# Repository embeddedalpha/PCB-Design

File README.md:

# PCB-Design    
Repository for PCB Design Projects

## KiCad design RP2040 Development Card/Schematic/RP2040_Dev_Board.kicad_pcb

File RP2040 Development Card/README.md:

# Raspberry Pi RP2040 Development Card

### Schematic : [RP2040_Dev_Board.pdf](https://github.com/embeddedalpha/PCB-Design/files/5889168/RP2040_Dev_Board.pdf)

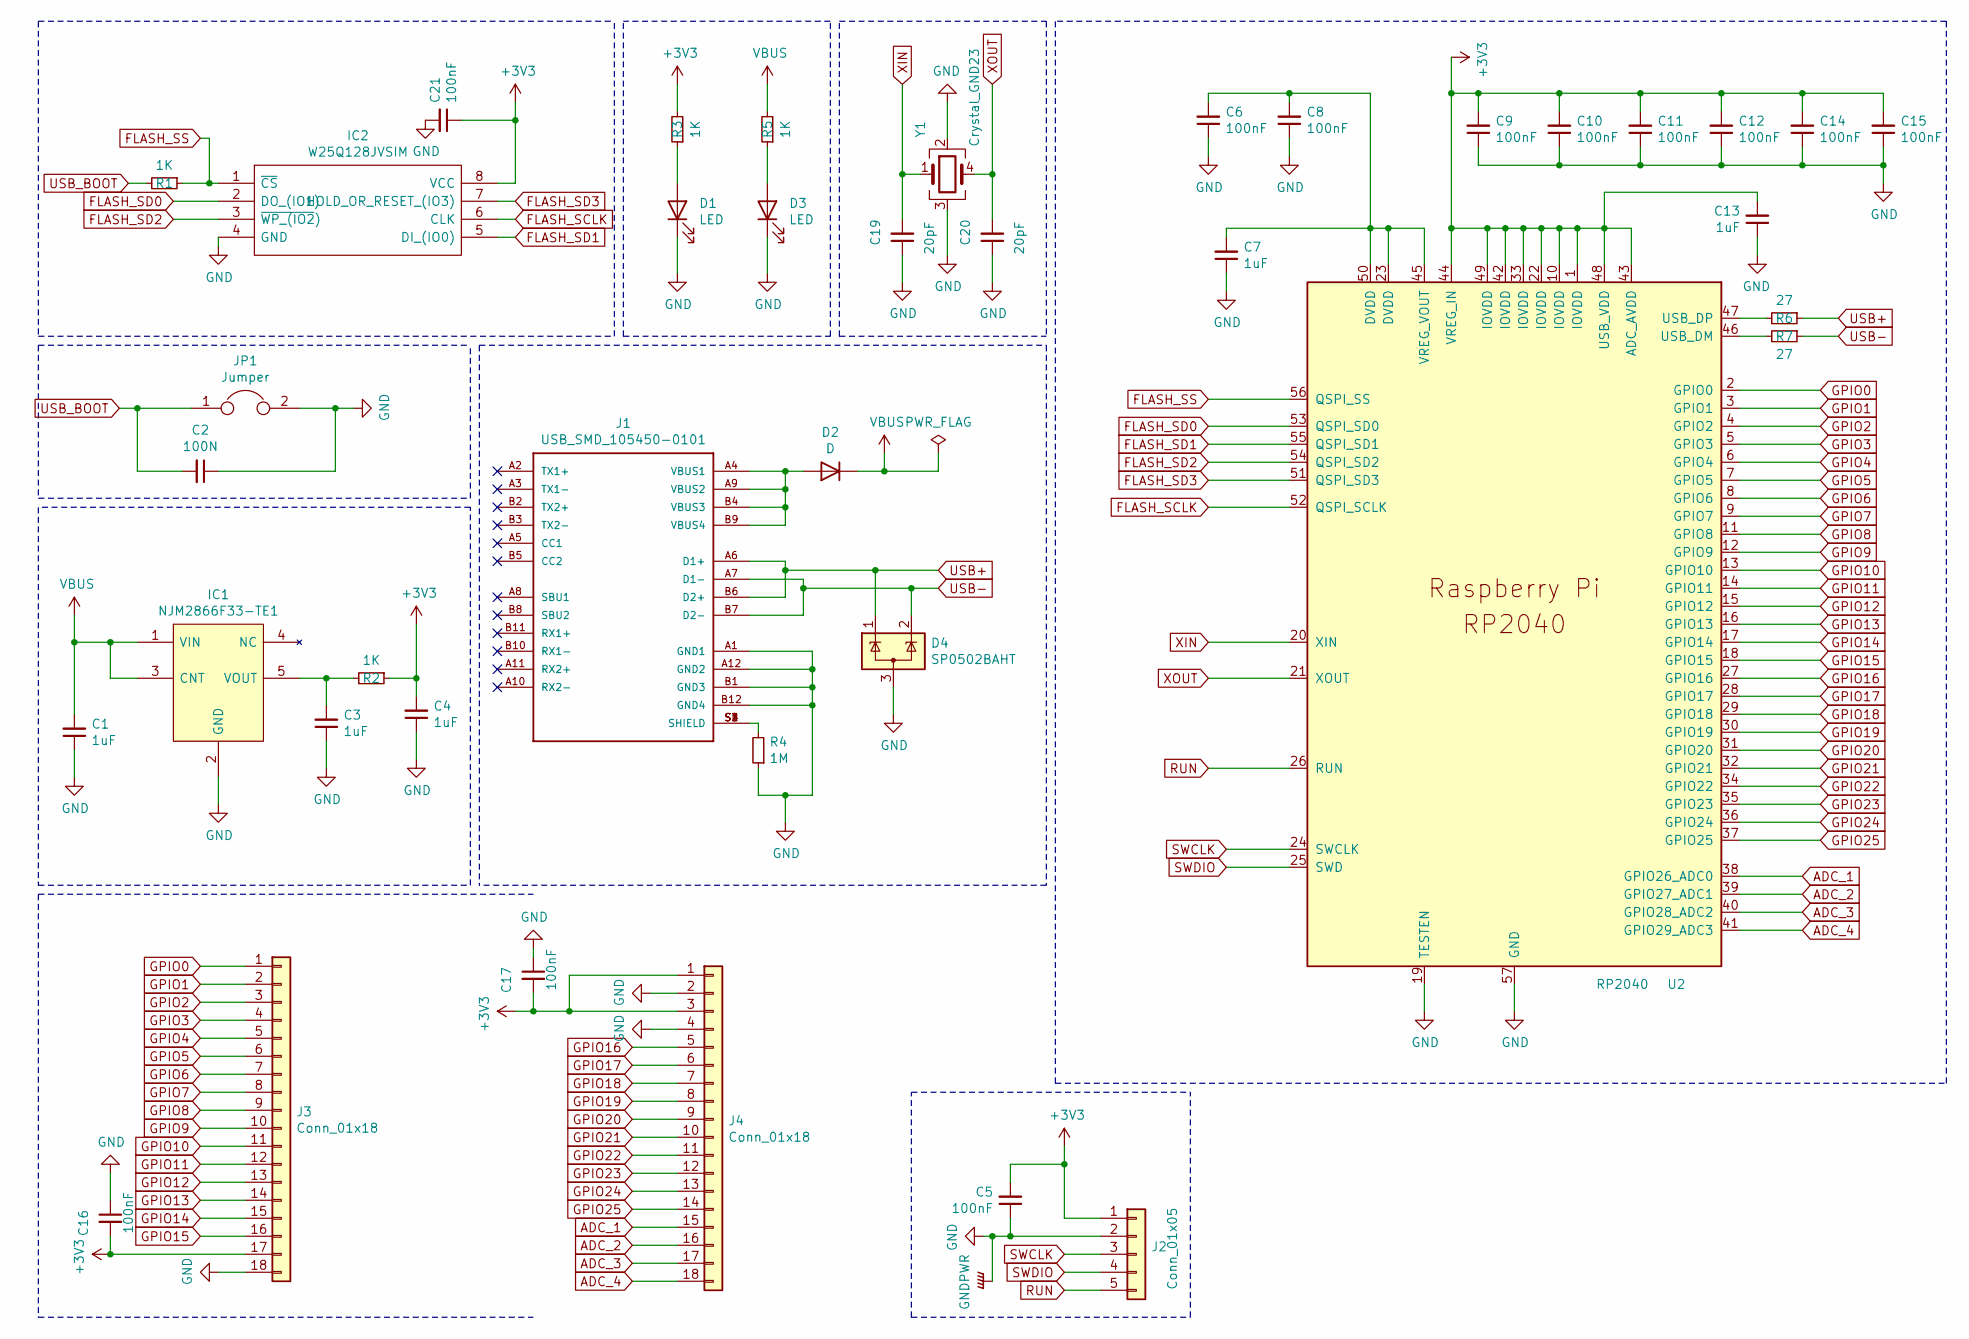
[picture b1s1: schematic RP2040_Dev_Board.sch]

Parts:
C1, C3, C4, C7, C13: 1uF; C_0402_1005Metric
C2: 100N; C_0402_1005Metric
C5, C6, C8, C9, C10, C11, C12, C14, C15, C16, C17, C21: 100nF; C_0402_1005Metric
C19, C20: 20pF; C_0402_1005Metric
D1, D3: LED; LED_0402_1005Metric
D2: D; D_0402_1005Metric
D4: SP0502BAHT; SOT-23
IC1: NJM2866F33-TE1; SOT95P280X130-5N; Mouser Part Number 513-NJM2866F33-TE1
IC2: W25Q128JVSIM; SOIC127P790X216-8N; Mouser Part Number 454-W25Q128JVSIM
J1: USB_SMD_105450-0101; MOLEX_105450-0101
J2: Conn_01x05; PinHeader_1x05_P2.54mm_Vertical
J3: Conn_01x18; Gold_Finger_1x18
J4: Conn_01x18; Gold_Finger_1x18B
JP1: Jumper
R1, R2, R3, R5: 1K; R_0402_1005Metric
R4: 1M; R_0402_1005Metric
R6, R7: 27; R_0402_1005Metric
U2: RP2040; RP2040-QFN-56
Y1: Crystal_GND23; ABM8AIG8000MHZ1ZT

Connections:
+3V3: C4.2, C5.2, C9.2, C10.2, C11.2, C12.2, C13.2, C14.2, C15.2, C16.2, C17.2, C21.1, IC2.8 (VCC), J2.1, J3.17, J4.1, J4.3, R2.1, R3.2, U2.1 (IOVDD), U2.10 (IOVDD), U2.22 (IOVDD), U2.33 (IOVDD), U2.42 (IOVDD), U2.43 (ADC_AVDD), U2.44 (VREG_IN), U2.48 (USB_VDD), U2.49 (IOVDD)
ADC_1: J4.15, U2.38 (GPIO26_ADC0)
ADC_2: J4.16, U2.39 (GPIO27_ADC1)
ADC_3: J4.17, U2.40 (GPIO28_ADC2)
ADC_4: J4.18, U2.41 (GPIO29_ADC3)
FLASH_SCLK: IC2.6 (CLK), U2.52 (QSPI_SCLK)
FLASH_SD0: IC2.2 (DO_(IO1)), U2.53 (QSPI_SD0)
FLASH_SD1: IC2.5 (DI_(IO0)), U2.55 (QSPI_SD1)
FLASH_SD2: IC2.3 (~WP_(IO2)), U2.54 (QSPI_SD2)
FLASH_SD3: IC2.7 (HOLD_OR_RESET_(IO3)), U2.51 (QSPI_SD3)
FLASH_SS: IC2.1 (~CS), R1.1, U2.56 (QSPI_SS)
GND: C1.1, C2.1, C3.1, C4.1, C5.1, C6.1, C7.1, C8.1, C9.1, C10.1, C11.1, C12.1, C13.1, C14.1, C15.1, C16.1, C17.1, C19.1, C20.1, C21.2, D1.1 (K), D3.1 (K), D4.3 (A), IC1.2 (GND), IC2.4 (GND), J1.A1 (GND1), J1.A12 (GND2), J1.B1 (GND3), J1.B12 (GND4), J2.2, J3.18, J4.2, J4.4, JP1.2, R4.1, U2.19 (TESTEN), U2.57 (GND), Y1.2, Y1.3
GPIO0: J3.1, U2.2 (GPIO0)
GPIO1: J3.2, U2.3 (GPIO1)
GPIO2: J3.3, U2.4 (GPIO2)
GPIO3: J3.4, U2.5 (GPIO3)
GPIO4: J3.5, U2.6 (GPIO4)
GPIO5: J3.6, U2.7 (GPIO5)
GPIO6: J3.7, U2.8 (GPIO6)
GPIO7: J3.8, U2.9 (GPIO7)
GPIO8: J3.9, U2.11 (GPIO8)
GPIO9: J3.10, U2.12 (GPIO9)
GPIO10: J3.11, U2.13 (GPIO10)
GPIO11: J3.12, U2.14 (GPIO11)
GPIO12: J3.13, U2.15 (GPIO12)
GPIO13: J3.14, U2.16 (GPIO13)
GPIO14: J3.15, U2.17 (GPIO14)
GPIO15: J3.16, U2.18 (GPIO15)
GPIO16: J4.5, U2.27 (GPIO16)
GPIO17: J4.6, U2.28 (GPIO17)
GPIO18: J4.7, U2.29 (GPIO18)
GPIO19: J4.8, U2.30 (GPIO19)
GPIO20: J4.9, U2.31 (GPIO20)
GPIO21: J4.10, U2.32 (GPIO21)
GPIO22: J4.11, U2.34 (GPIO22)
GPIO23: J4.12, U2.35 (GPIO23)
GPIO24: J4.13, U2.36 (GPIO24)
GPIO25: J4.14, U2.37 (GPIO25)
unnamed: C3.2, IC1.5 (VOUT), R2.2
unnamed: C6.2, C7.2, C8.2, U2.23 (DVDD), U2.45 (VREG_VOUT), U2.50 (DVDD)
unnamed: D1.2 (A), R3.1
unnamed: D2.2 (A), J1.A4 (VBUS1), J1.A9 (VBUS2), J1.B4 (VBUS3), J1.B9 (VBUS4)
unnamed: D3.2 (A), R5.1
unnamed: J1.S1 (SHIELD), J1.S2 (SHIELD), J1.S3 (SHIELD), J1.S4 (SHIELD), R4.2
unnamed: R6.2, U2.47 (USB_DP)
unnamed: R7.2, U2.46 (USB_DM)
RUN: J2.5, U2.26 (RUN)
SWCLK: J2.3, U2.24 (SWCLK)
SWDIO: J2.4, U2.25 (SWD)
USB+: D4.1 (K), J1.A6 (D1+), J1.B6 (D2+), R6.1
USB-: D4.2 (K), J1.A7 (D1-), J1.B7 (D2-), R7.1
USB_BOOT: C2.2, JP1.1, R1.2
VBUS: C1.2, D2.1 (K), IC1.1 (VIN), IC1.3 (CNT), R5.2
XIN: C19.2, U2.20 (XIN), Y1.1
XOUT: C20.2, U2.21 (XOUT), Y1.4

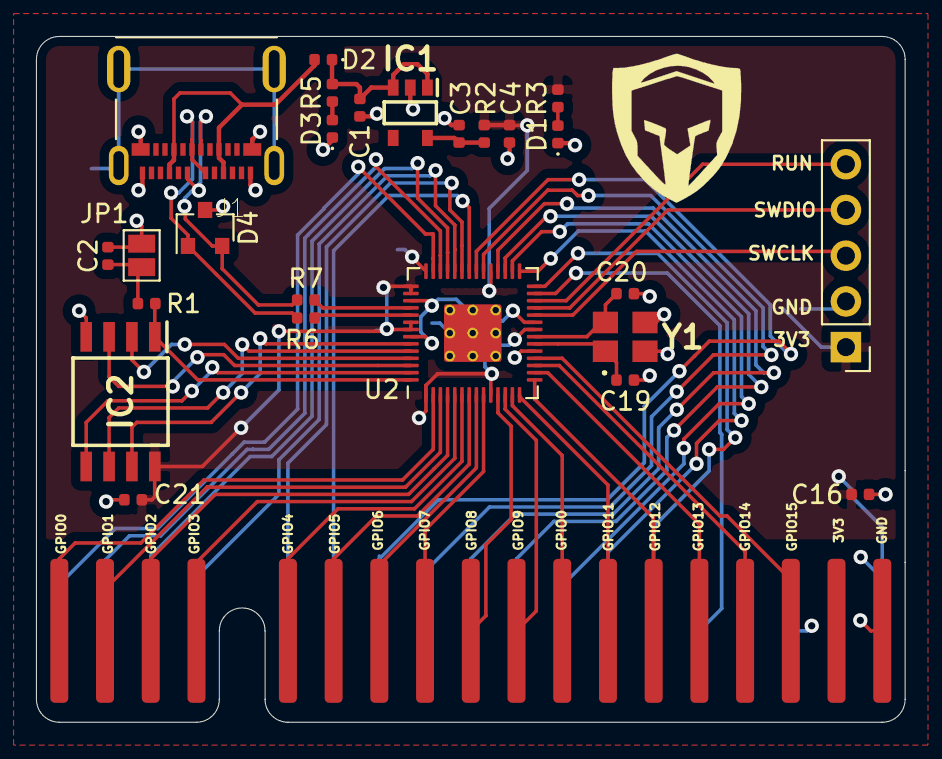
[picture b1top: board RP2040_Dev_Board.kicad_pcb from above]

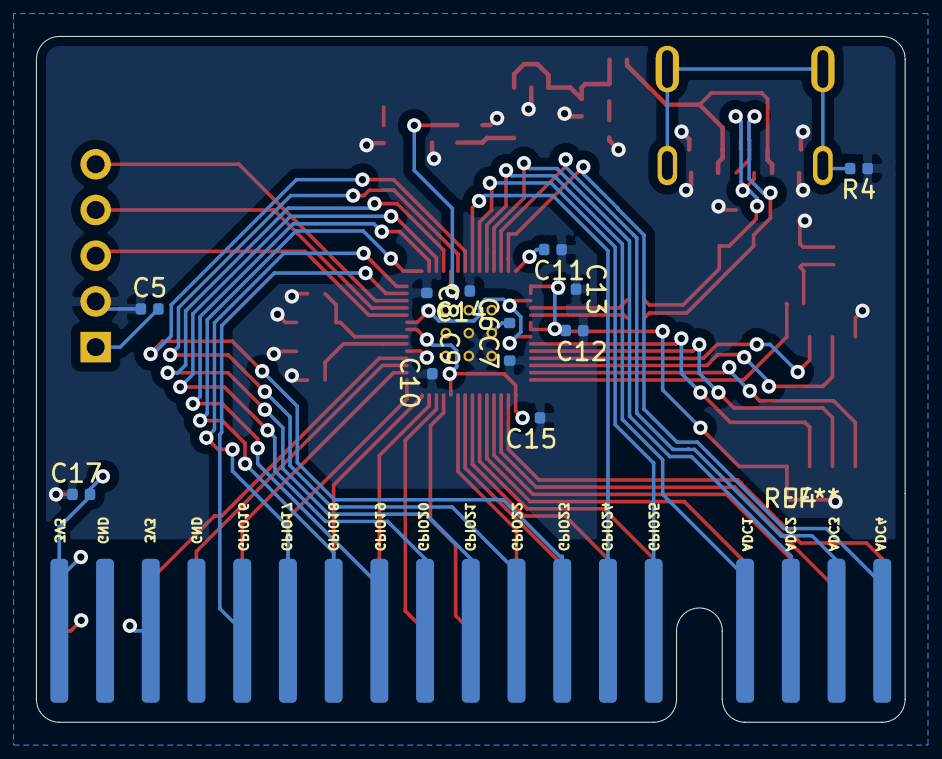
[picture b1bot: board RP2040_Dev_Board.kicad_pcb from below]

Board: 2 copper layers, 48.3 x 38.1 mm, 40 parts (13 on the bottom side), 55 nets.

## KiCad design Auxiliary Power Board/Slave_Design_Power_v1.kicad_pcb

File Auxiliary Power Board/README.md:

# Auxiliary Power Board

<h4> 
This board is a daughterboard of a IIoT Data Acquistion Board. The board rectifies one 18V AC and one 12V AC power input and regulates them to produce clean 16-17V DC and 11-12V DC power. The board also supplies 5V DC power to main control board and also provide connectors to control high power relays so that they are isolated from sensitive devices
</h4>

## View 1

## View 2

## View 3

### Gerber Files: [Gerber.zip](https://github.com/embeddedalpha/PCB-Design/files/5765942/Gerber.zip)

### DXF Files: [DXF.zip](https://github.com/embeddedalpha/PCB-Design/files/5765948/DXF.zip)

### STEP File: [3D.zip](https://github.com/embeddedalpha/PCB-Design/files/5765976/3D.zip)

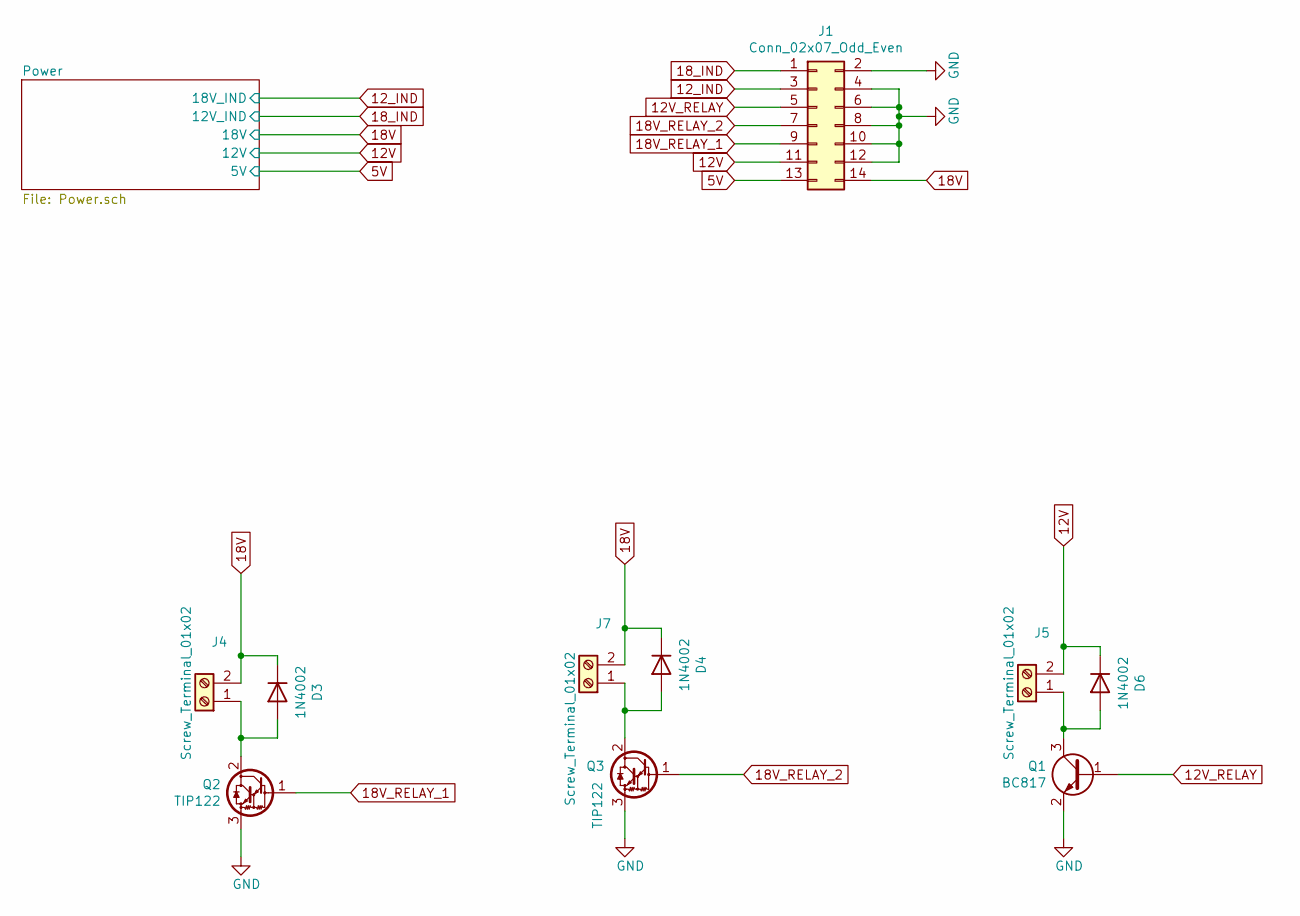
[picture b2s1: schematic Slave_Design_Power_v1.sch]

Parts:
D3, D4, D6: 1N4002; D_DO-41_SOD81_P10.16mm_Horizontal
J1: Conn_02x07_Odd_Even; PinSocket_2x07_P2.54mm_Vertical
J4, J5, J7: Screw_Terminal_01x02; TerminalBlock_Phoenix_MKDS-1,5-2-5.08_1x02_P5.08mm_Horizont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
Q1: BC817; SOT-23
Q2, Q3: TIP122; TO-220-3_Vertical

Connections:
5V: J1.13; also elsewhere on the board
12V: D6.1 (K), J1.11, J5.2; also elsewhere on the board
12V_RELAY: J1.5, Q1.1 (B)
12_IND: J1.3; also elsewhere on the board
18V: D3.1 (K), D4.1 (K), J1.14, J4.2, J7.2; also elsewhere on the board
18V_RELAY_1: J1.9, Q2.1 (B)
18V_RELAY_2: J1.7, Q3.1 (B)
18_IND: J1.1; also elsewhere on the board
GND: J1.2, J1.4, J1.6, J1.8, J1.10, J1.12, Q1.2 (E), Q2.3 (E), Q3.3 (E); also elsewhere on the board
unnamed: D3.2 (A), J4.1, Q2.2 (C)
unnamed: D4.2 (A), J7.1, Q3.2 (C)
unnamed: D6.2 (A), J5.1, Q1.3 (C)

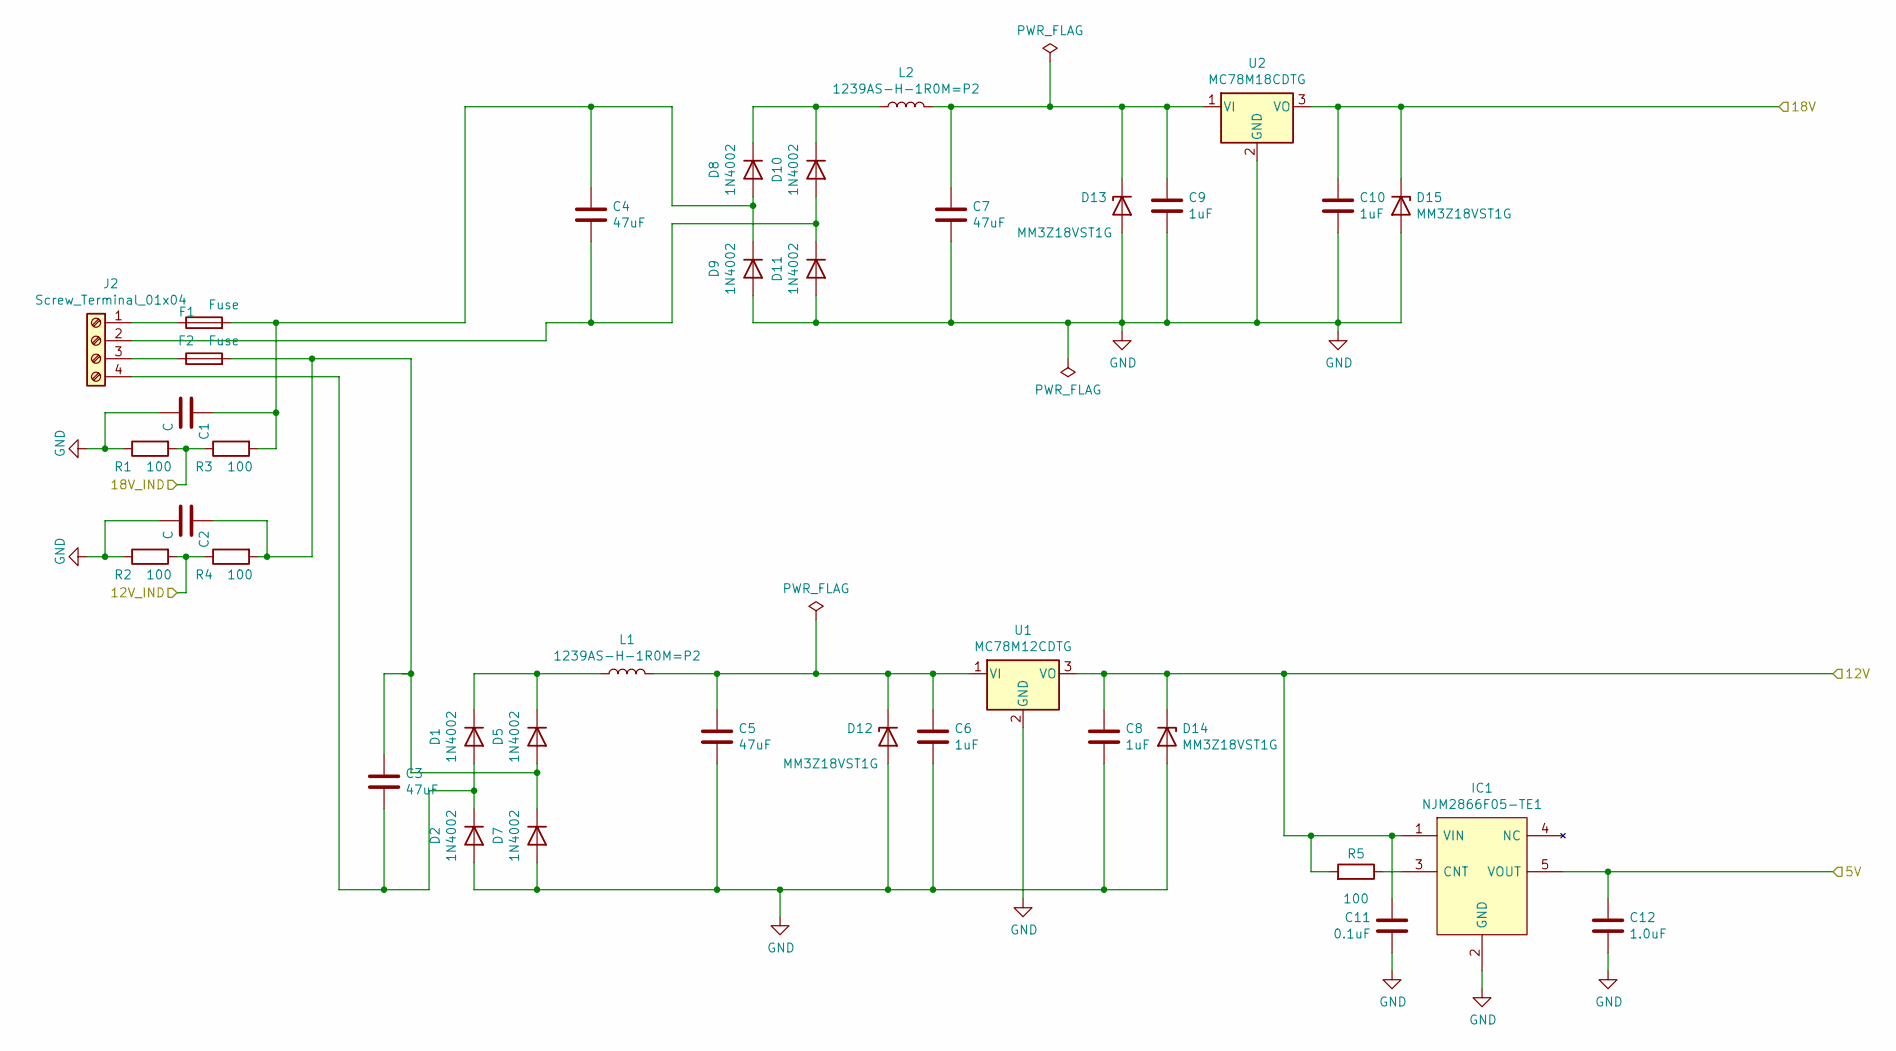
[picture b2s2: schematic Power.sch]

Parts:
C1, C2: C; C_0805_2012Metric_Pad1.15x1.40mm_HandSolder
C3, C4, C5, C7: 47uF; CP_Radial_D8.0mm_P5.00mm; Part APXG200ARA470ME61G
C6, C8, C9, C10: 1uF; CP_Elec_5x4.5
C11: 0.1uF; CP_Elec_5x4.5
C12: 1.0uF; CP_Elec_5x4.5
D1, D2, D5, D7, D8, D9, D10, D11: 1N4002; D_DO-41_SOD81_P10.16mm_Horizontal
D12, D13, D14, D15: MM3Z18VST1G; D_SOD-123F
F1, F2: Fuse; Fuse_BelFuse_0ZRE0005FF_L8.3mm_W3.8mm
IC1: NJM2866F05-TE1; SOT95P280X130-5N; Mouser Part Number 513-NJM2866F33-TE1
J2: Screw_Terminal_01x04; TerminalBlock_Phoenix_MKDS-1,5-4-5.08_1x04_P5.08mm_Horizont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
L1, L2: 1239AS-H-1R0M=P2; L_1008_2520Metric
R1, R2, R3, R4, R5: 100; R_0805_2012Metric_Pad1.15x1.40mm_HandSolder
U1: MC78M12CDTG; TO-252-2
U2: MC78M18CDTG; TO-252-2

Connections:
5V: C12.1, IC1.5 (VOUT); also elsewhere on the board
12V: C8.1, C11.1, D14.1 (K), IC1.1 (VIN), R5.2, U1.3 (VO); also elsewhere on the board
12_IND: R1.2, R3.1; also elsewhere on the board
18V: C10.1, D15.1 (K), U2.3 (VO); also elsewhere on the board
18_IND: R2.2, R4.1; also elsewhere on the board
GND: C1.2, C2.2, C5.2, C6.2, C7.2, C8.2, C9.2, C10.2, C11.2, C12.2, D2.2 (A), D7.2 (A), D9.2 (A), D11.2 (A), D12.2 (A), D13.2 (A), D14.2 (A), D15.2 (A), IC1.2 (GND), R1.1, R2.1, U1.2 (GND), U2.2 (GND); also elsewhere on the board
unnamed: C1.1, C4.1, D8.2 (A), D9.1 (K), F1.2, R3.2
unnamed: C2.1, C3.1, D5.2 (A), D7.1 (K), F2.2, R4.2
unnamed: C3.2, D1.2 (A), D2.1 (K), J2.4
unnamed: C4.2, D10.2 (A), D11.1 (K), J2.2
unnamed: C5.1, C6.1, D12.1 (K), L1.2, U1.1 (VI)
unnamed: C7.1, C9.1, D13.1 (K), L2.2, U2.1 (VI)
unnamed: D1.1 (K), D5.1 (K), L1.1
unnamed: D8.1 (K), D10.1 (K), L2.1
unnamed: F1.1, J2.1
unnamed: F2.1, J2.3
unnamed: IC1.3 (CNT), R5.1

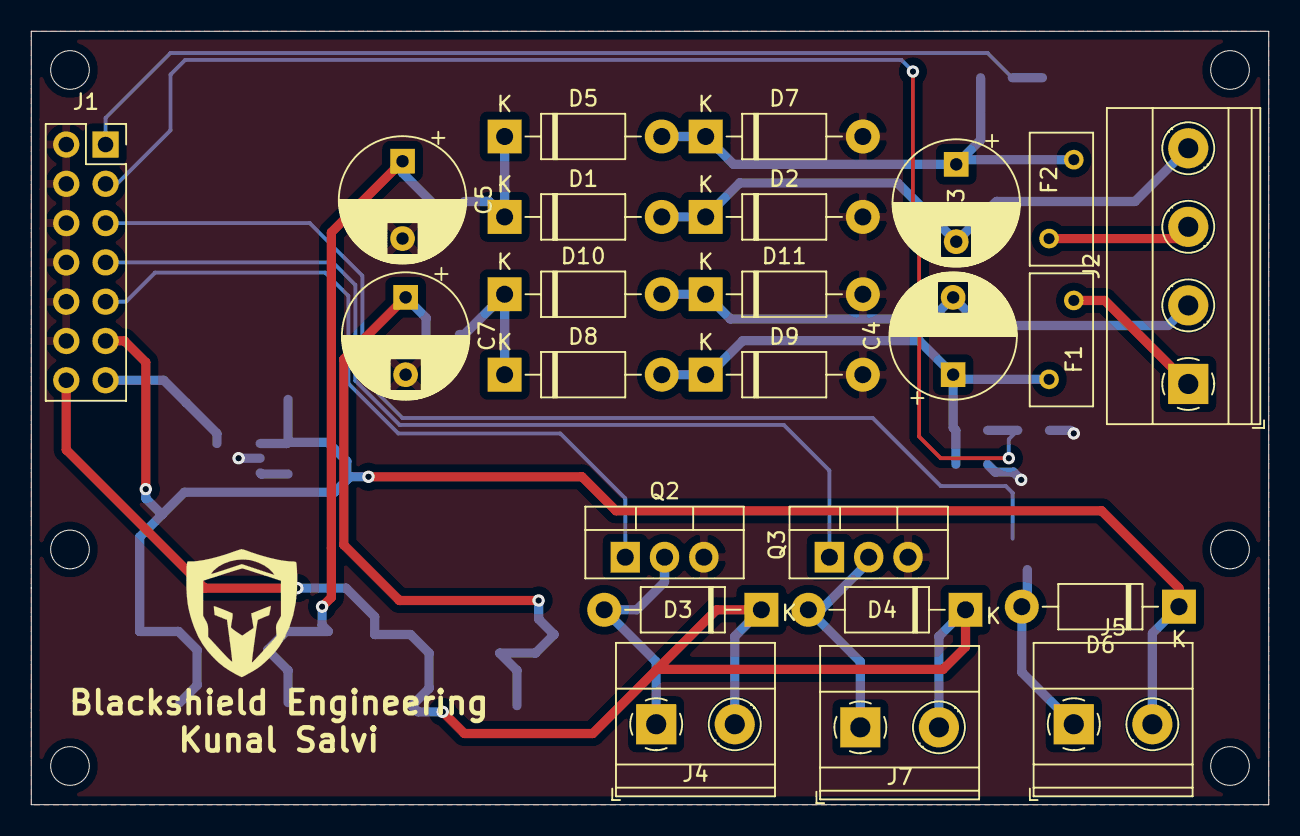
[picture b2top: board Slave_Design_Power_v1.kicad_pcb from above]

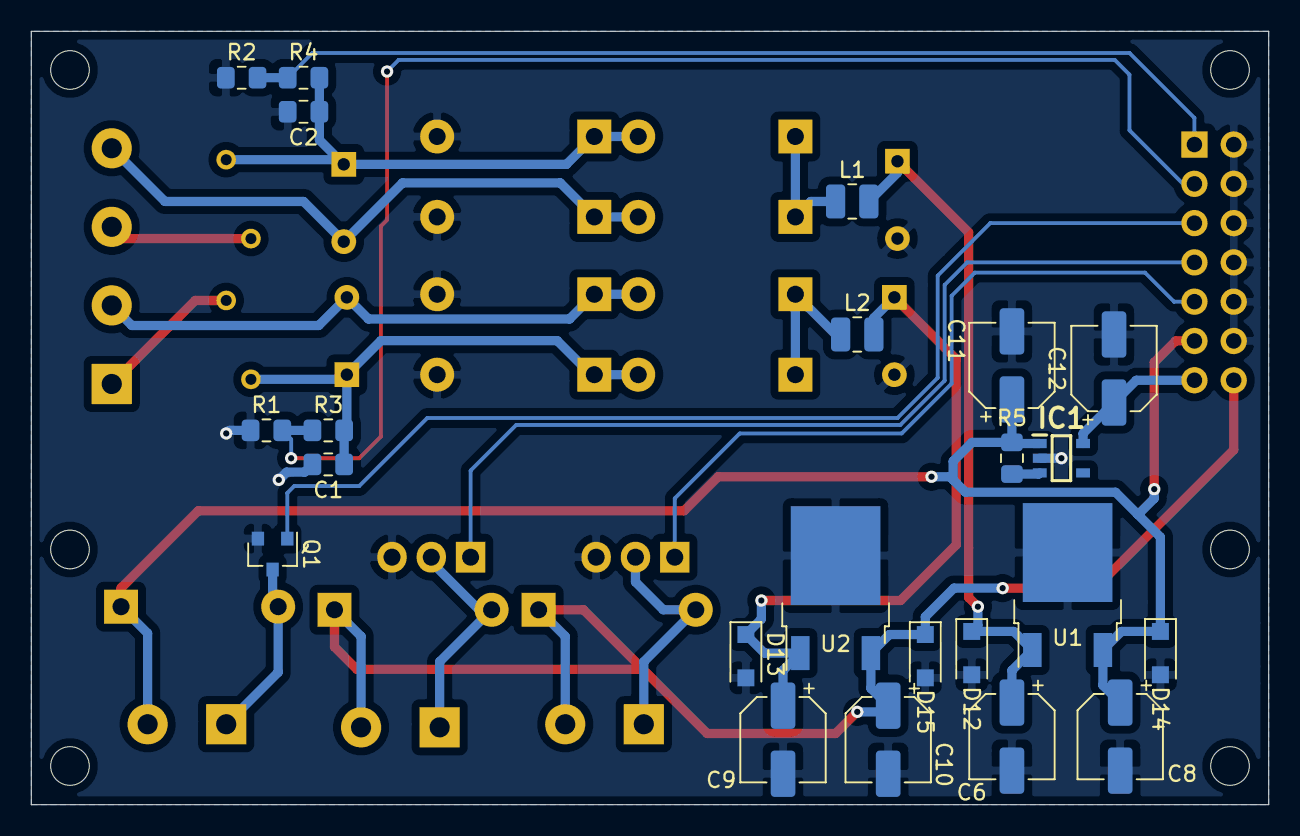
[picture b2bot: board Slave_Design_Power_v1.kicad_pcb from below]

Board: 2 copper layers, 80.0 x 50.0 mm, 47 parts (23 on the bottom side), 23 nets.

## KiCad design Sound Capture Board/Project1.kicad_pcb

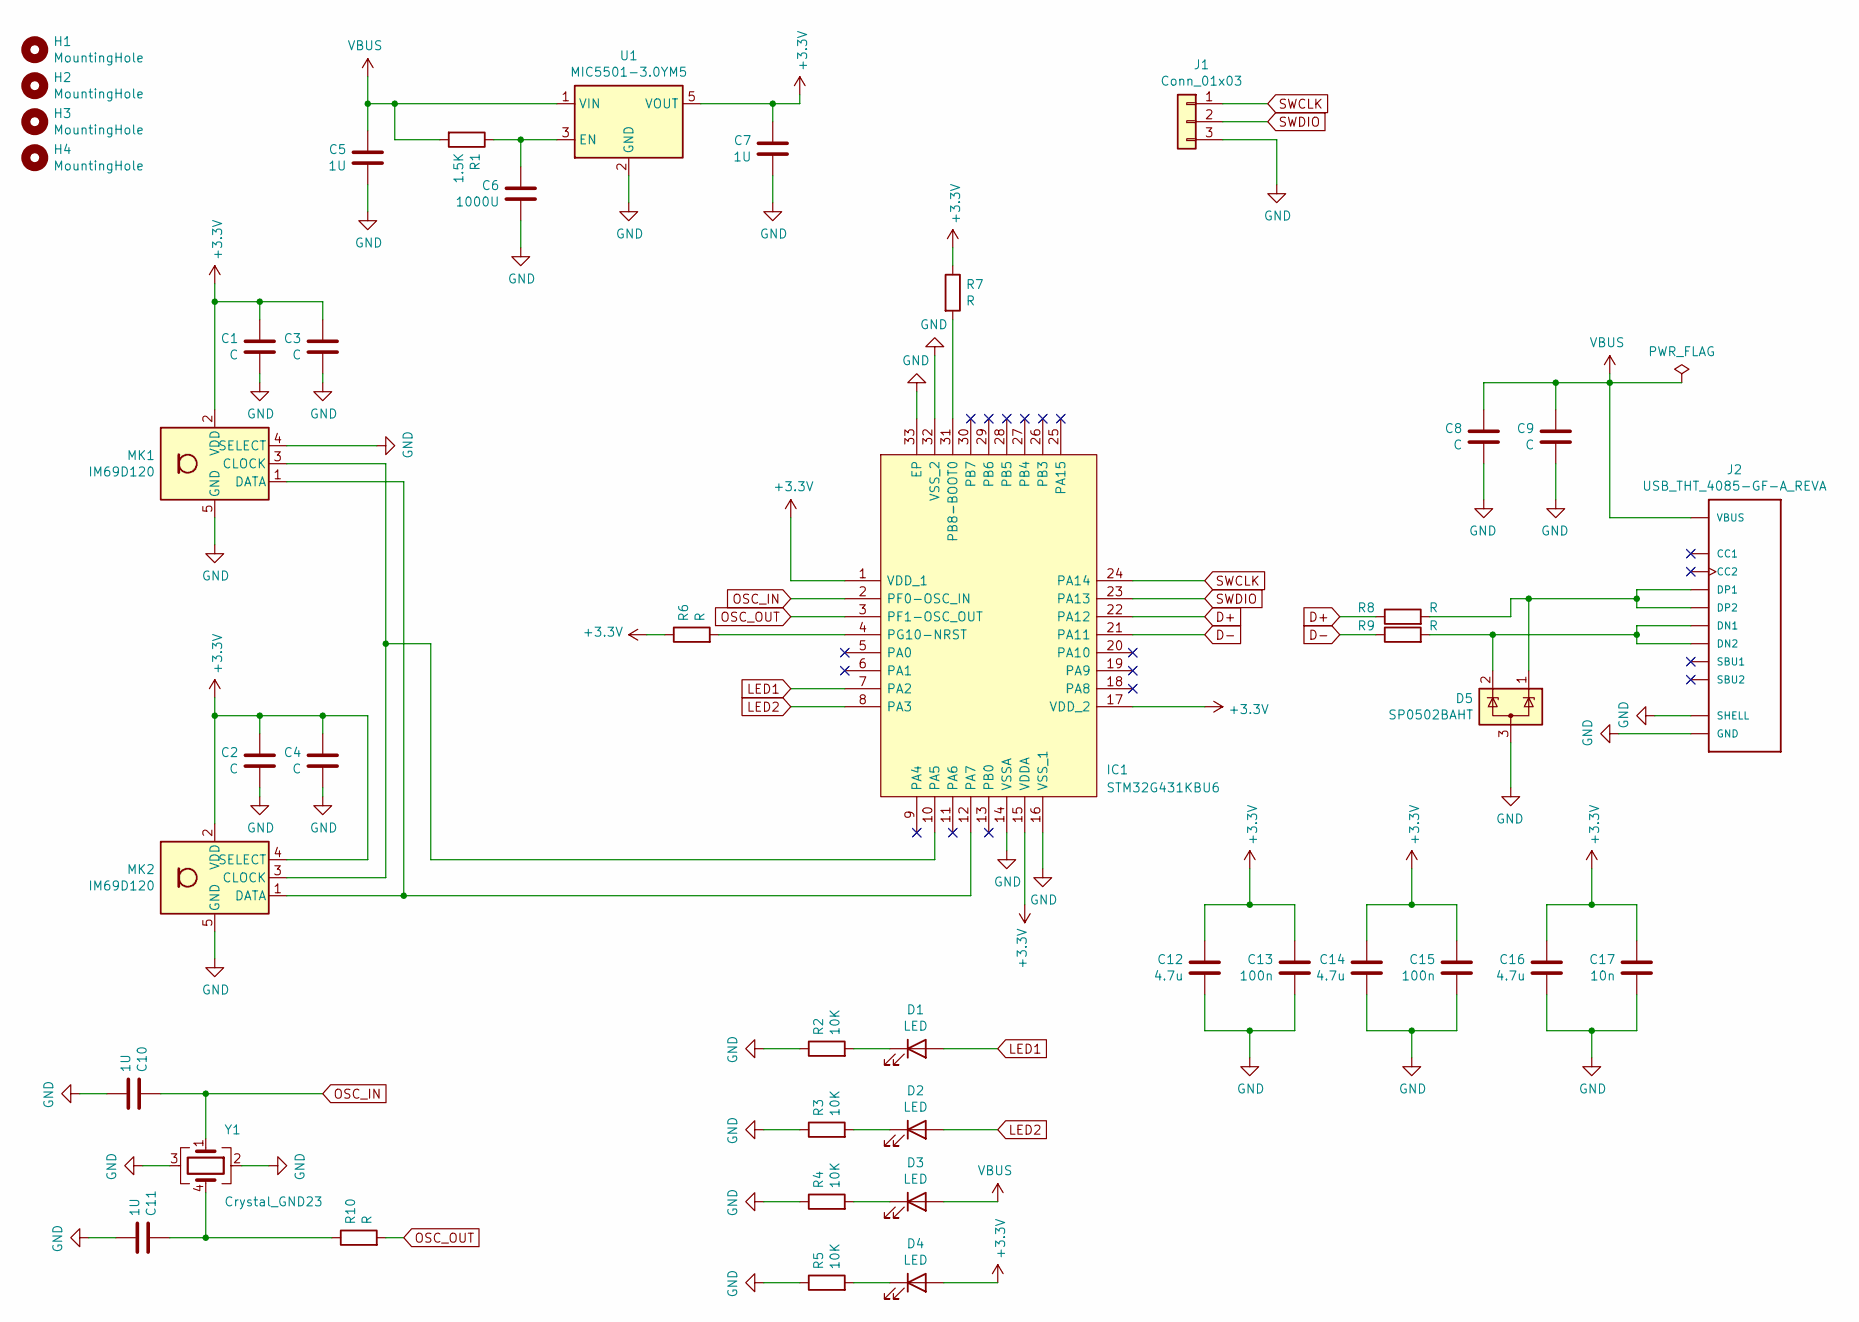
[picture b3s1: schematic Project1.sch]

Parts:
C1, C2, C3, C4, C8, C9: C; C_0603_1608Metric
C5, C7, C10, C11: 1U; C_0603_1608Metric
C6: 1000U; C_0603_1608Metric
C12, C14, C16: 4.7u; C_0603_1608Metric
C13, C15: 100n; C_0603_1608Metric
C17: 10n; C_0603_1608Metric
D1, D2, D3, D4: LED; LED_0603_1608Metric
D5: SP0502BAHT; SOT-23
H1, H2, H3, H4: MountingHole; MountingHole_3.2mm_M3_Pad_Via
IC1: STM32G431KBU6; QFN50P500X500X60-33N-D; Mouser Part Number 511-STM32G431KBU6
J1: Conn_01x03; PinHeader_1x03_P2.54mm_Horizontal
J2: USB_THT_4085-GF-A_REVA; GCT_USB4085-GF-A_REVA
MK1, MK2: IM69D120; Infineon_PG-LLGA-5-1
R1: 1.5K; R_0603_1608Metric_Pad1.05x0.95mm_HandSolder
R2, R3, R4, R5: 10K; R_0603_1608Metric_Pad1.05x0.95mm_HandSolder
R6, R7, R8, R9, R10: R; R_0603_1608Metric_Pad1.05x0.95mm_HandSolder
U1: MIC5501-3.0YM5; SOT-23-5
Y1: Crystal_GND23; Crystal_SMD_TXC_7M-4Pin_3.2x2.5mm

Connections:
+3V3: C1.1, C2.1, C3.1, C4.1, C7.1, C12.1, C13.1, C14.1, C15.1, C16.1, C17.1, D4.2 (A), IC1.1 (VDD_1), IC1.15 (VDDA), IC1.17 (VDD_2), MK1.2 (VDD), MK2.2 (VDD), MK2.4 (SELECT), R6.1, R7.1, U1.5 (VOUT)
D+: IC1.22 (PA12), R8.1
D-: IC1.21 (PA11), R9.1
GND: C1.2, C2.2, C3.2, C4.2, C5.2, C6.2, C7.2, C8.2, C9.2, C10.2, C11.2, C12.2, C13.2, C14.2, C15.2, C16.2, C17.2, D5.3 (A), IC1.14 (VSSA), IC1.16 (VSS_1), IC1.32 (VSS_2), IC1.33 (EP), J1.3, J2.A1 (GND), J2.A12 (GND), J2.B1 (GND), J2.B12 (GND), J2.P1 (SHELL), J2.P2 (SHELL), J2.P3 (SHELL), J2.P4 (SHELL), MK1.4 (SELECT), MK1.5 (GND), MK2.5 (GND), R2.1, R3.1, R4.1, R5.1, U1.2 (GND), Y1.2, Y1.3
LED1: D1.2 (A), IC1.7 (PA2)
LED2: D2.2 (A), IC1.8 (PA3)
unnamed: C6.1, R1.1, U1.3 (EN)
unnamed: C11.1, R10.1, Y1.4
unnamed: D1.1 (K), R2.2
unnamed: D2.1 (K), R3.2
unnamed: D3.1 (K), R4.2
unnamed: D4.1 (K), R5.2
unnamed: D5.1 (K), J2.A6 (DP1), J2.B6 (DP2), R8.2
unnamed: D5.2 (K), J2.A7 (DN1), J2.B7 (DN2), R9.2
unnamed: IC1.4 (PG10-NRST), R6.2
unnamed: IC1.10 (PA5), MK1.3 (CLOCK), MK2.3 (CLOCK)
unnamed: IC1.12 (PA7), MK1.1 (DATA), MK2.1 (DATA)
unnamed: IC1.31 (PB8-BOOT0), R7.2
OSC_IN: C10.1, IC1.2 (PF0-OSC_IN), Y1.1
OSC_OUT: IC1.3 (PF1-OSC_OUT), R10.2
SWCLK: IC1.24 (PA14), J1.1
SWDIO: IC1.23 (PA13), J1.2
VBUS: C5.1, C8.1, C9.1, D3.2 (A), J2.A4 (VBUS), J2.A9 (VBUS), J2.B4 (VBUS), J2.B9 (VBUS), R1.2, U1.1 (VIN)

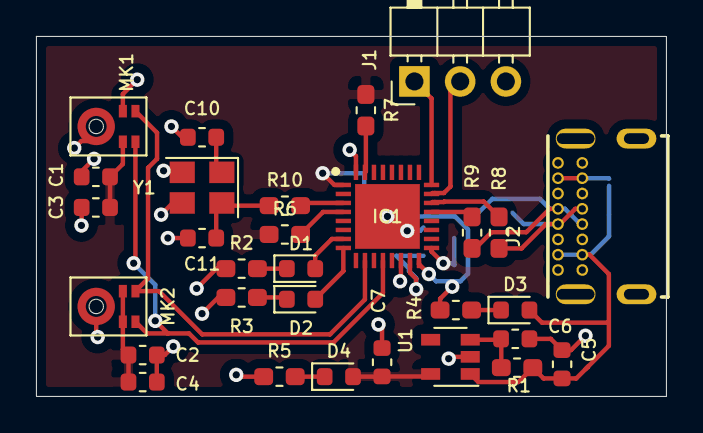
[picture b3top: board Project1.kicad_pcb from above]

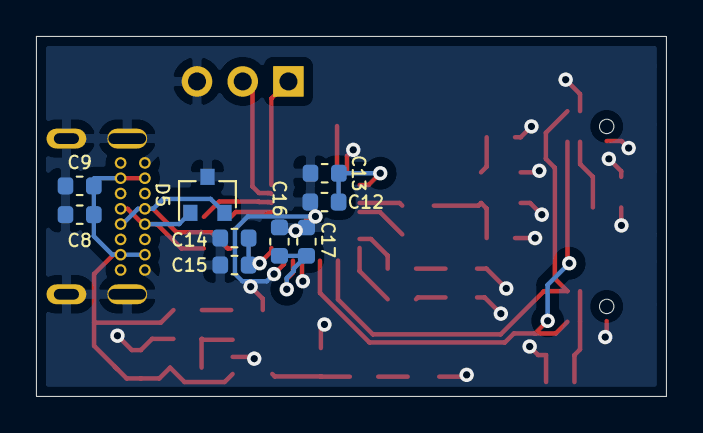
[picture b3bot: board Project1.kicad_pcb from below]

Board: 2 copper layers, 35.0 x 20.0 mm, 39 parts (9 on the bottom side), 23 nets.

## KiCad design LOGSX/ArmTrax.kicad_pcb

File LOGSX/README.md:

<H1> LOGSX: Low Power Logistic Tracker </H1>

[ArmTrax.pdf](https://github.com/embeddedalpha/PCB-Design/files/4638654/ArmTrax.pdf)

<H4> 1:  </H4>

<H4> 2:  </H4>

<H4> 3:  </H4>

<H4> 4:  </H4>

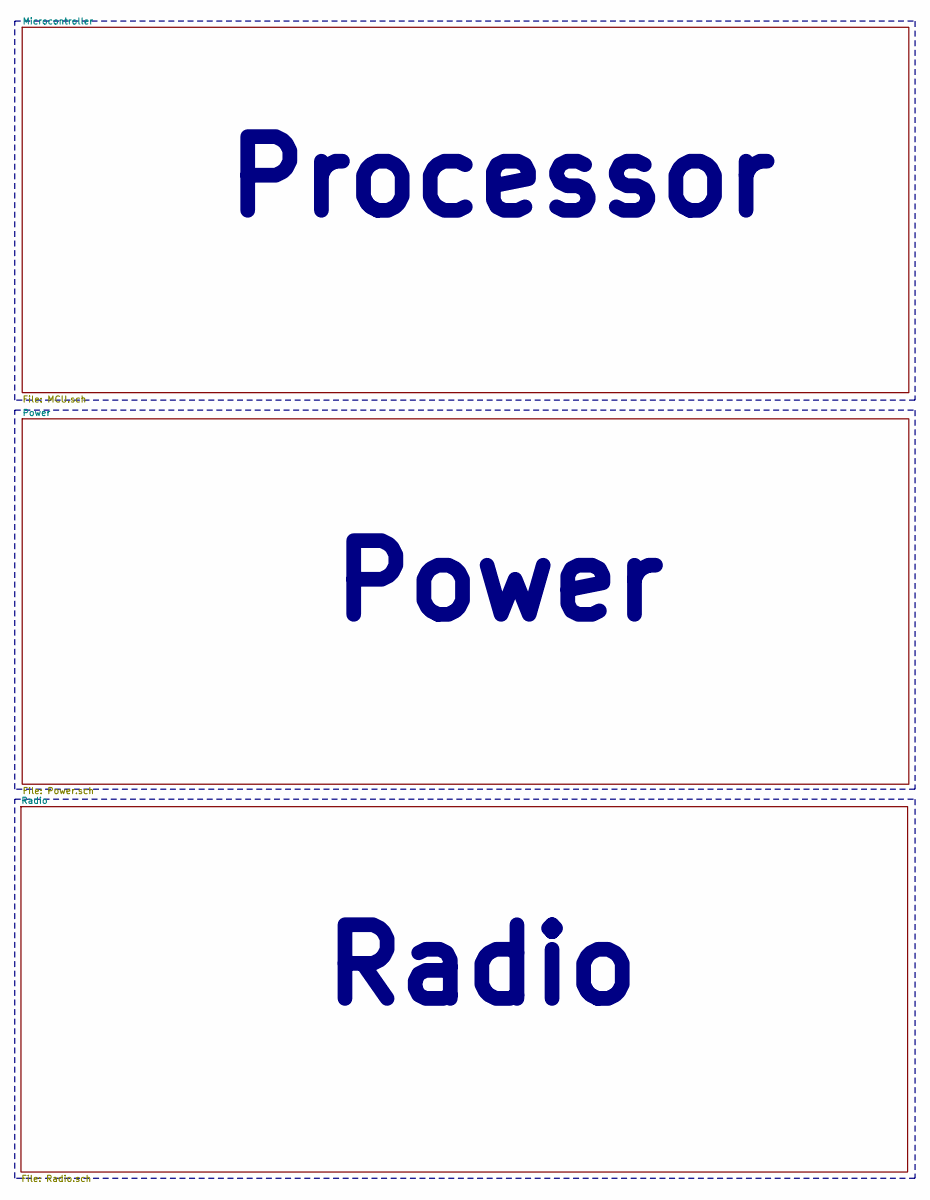
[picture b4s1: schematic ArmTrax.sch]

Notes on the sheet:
Radio
Power
Processor

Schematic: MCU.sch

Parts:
C1, C2, C3, C4, C5: 2.2pF; C_0201_0603Metric
C6: 1uF; C_0402_1005Metric
C7, C8: 1pF; C_0201_0603Metric
C9, C10, C11, C12: 2.2pF; C_0402_1005Metric
IC1: STM32G473CET6; QFN-48-1EP_7x7mm_P0.5mm_EP5.45x5.45mm; Mouser Part Number 511-STM32G473CET6
J1: Conn_01x02; BatteryHolder_Keystone_3008_1x2450
JP1: SolderJumper_3_Open; SolderJumper-3_P1.3mm_Open_Pad1.0x1.5mm_NumberLabels
R1: 1K7; R_0402_1005Metric
R2, R3: 4.7K; R_0402_1005Metric
TP1, TP2, TP3: TestPoint; TestPoint_Keystone_5015_Micro-Minature
U1: W25Q32JVSS; SOIC-8_5.23x5.23mm_P1.27mm
Y1: Crystal_GND24; Crystal_SMD_Abracon_ABM8G-4Pin_3.2x2.5mm
Y2: Crystal_GND24; Crystal_SMD_SeikoEpson_MA506-4Pin_12.7x5.1mm

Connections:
FLASH_NSS: U1.1 (~CS); also elsewhere on the board
MISO: U1.2 (DO(IO1)); also elsewhere on the board
MOSI: U1.5 (DI(IO0)); also elsewhere on the board
unnamed 9: C3.1, JP1.2 (C); also elsewhere on the board
unnamed: JP1.1 (A), R1.2
OSC32_IN: C7.1, Y2.1; also elsewhere on the board
OSC32_OUT: C8.1, Y2.4; also elsewhere on the board
OSC_IN: C1.1, Y1.1; also elsewhere on the board
OSC_OUT: C2.1, Y1.4; also elsewhere on the board
SCK: U1.6 (CLK); also elsewhere on the board
SCL: R2.2; also elsewhere on the board
SDA: R3.2; also elsewhere on the board
SWCLK: TP1.1; also elsewhere on the board
SWDIO: TP2.1; also elsewhere on the board

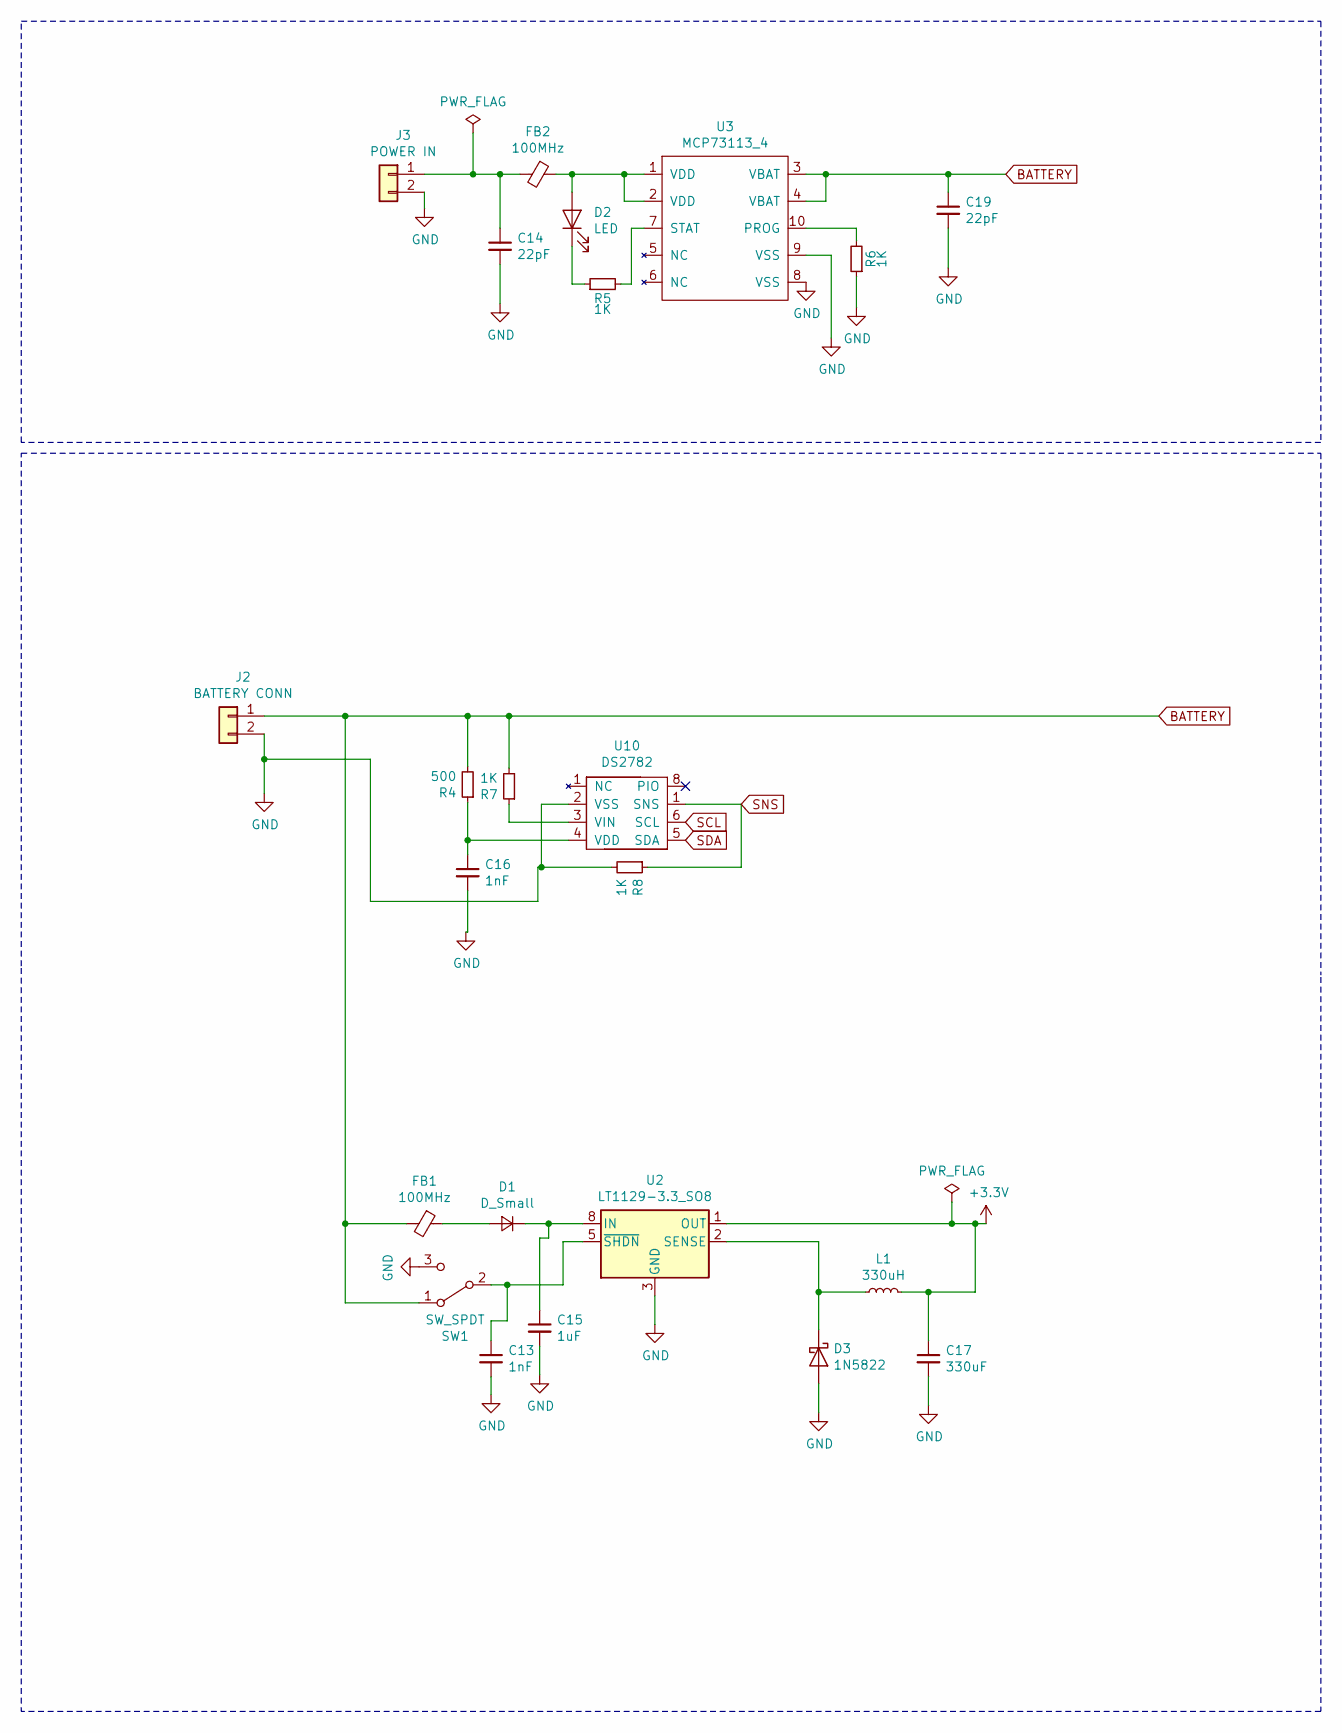
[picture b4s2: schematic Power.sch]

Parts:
C13, C16: 1nF; C_0201_0603Metric
C14, C19: 22pF; C_0402_1005Metric
C15: 1uF; C_0402_1005Metric
C17: 330uF; C_0402_1005Metric
D1: D_Small; D_0402_1005Metric
D2: LED; LED_0402_1005Metric
D3: 1N5822; D_0402_1005Metric
FB1, FB2: 100MHz; L_0402_1005Metric
J2: BATTERY CONN; BatteryHolder_Keystone_1042_1x18650
J3: POWER IN; JST_PH_B2B-PH-SM4-TB_1x02-1MP_P2.00mm_Vertical
L1: 330uH; L_0402_1005Metric
R4: 500; R_0402_1005Metric
R5, R6, R7, R8: 1K; R_0402_1005Metric
SW1: SW_SPDT; SW_SPDT_CK-JS102011SAQN
U2: LT1129-3.3_SO8; SOIC-8_3.9x4.9mm_P1.27mm
U3: MCP73113_4; MCP73113
U10: DS2782; TSSOP-8_4.4x3mm_P0.65mm

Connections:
BATTERY: C19.1, FB1.2, J2.1, R4.2, R7.2, SW1.1 (A), U3.3 (VBAT), U3.4 (VBAT)
unnamed: C13.1, SW1.2 (B), U2.5 (~SHDN)
unnamed: C14.1, FB2.2, J3.1
unnamed: C15.1, D1.1 (K), U2.8 (IN)
unnamed: C16.1, R4.1, U10.4 (VDD)
unnamed: D1.2 (A), FB1.1
unnamed: D2.1 (K), R5.1
unnamed: D2.2 (A), FB2.1, U3.1 (VDD), U3.2 (VDD)
unnamed: D3.1 (K), L1.1, U2.2 (SENSE)
unnamed: R5.2, U3.7 (STAT)
unnamed: R6.2, U3.10 (PROG)
unnamed: R7.1, U10.3 (VIN)
SCL: U10.6 (SCL); also elsewhere on the board
SDA: U10.5 (SDA); also elsewhere on the board
